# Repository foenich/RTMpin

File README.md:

# RTMpin
This is a pinball project.

A Rollergames playfield was turned into a hybrid pinball machine (pinball firmware via PinMAME like in virtual pinball, but with real playfield and steel balls).

The emulator PinMAME runs on a Raspberry Pi and controls sound, DMD and a few IO-boards underneath the playfield. These in turn read the switch positions and activates the coils and lamps.

To watch a video see documentation folder: rg1stgame.mp4

A word of warning: this is a private, non commercial hobby project. Hardware and software still has errors (see issues and Changes.txt). To make use of anything of this project a basic understanding of electronics and programming is necessary. Nothing of it is "plug and play". I'm surely not liable for any damage to assemblies, pinball machines or even persons.

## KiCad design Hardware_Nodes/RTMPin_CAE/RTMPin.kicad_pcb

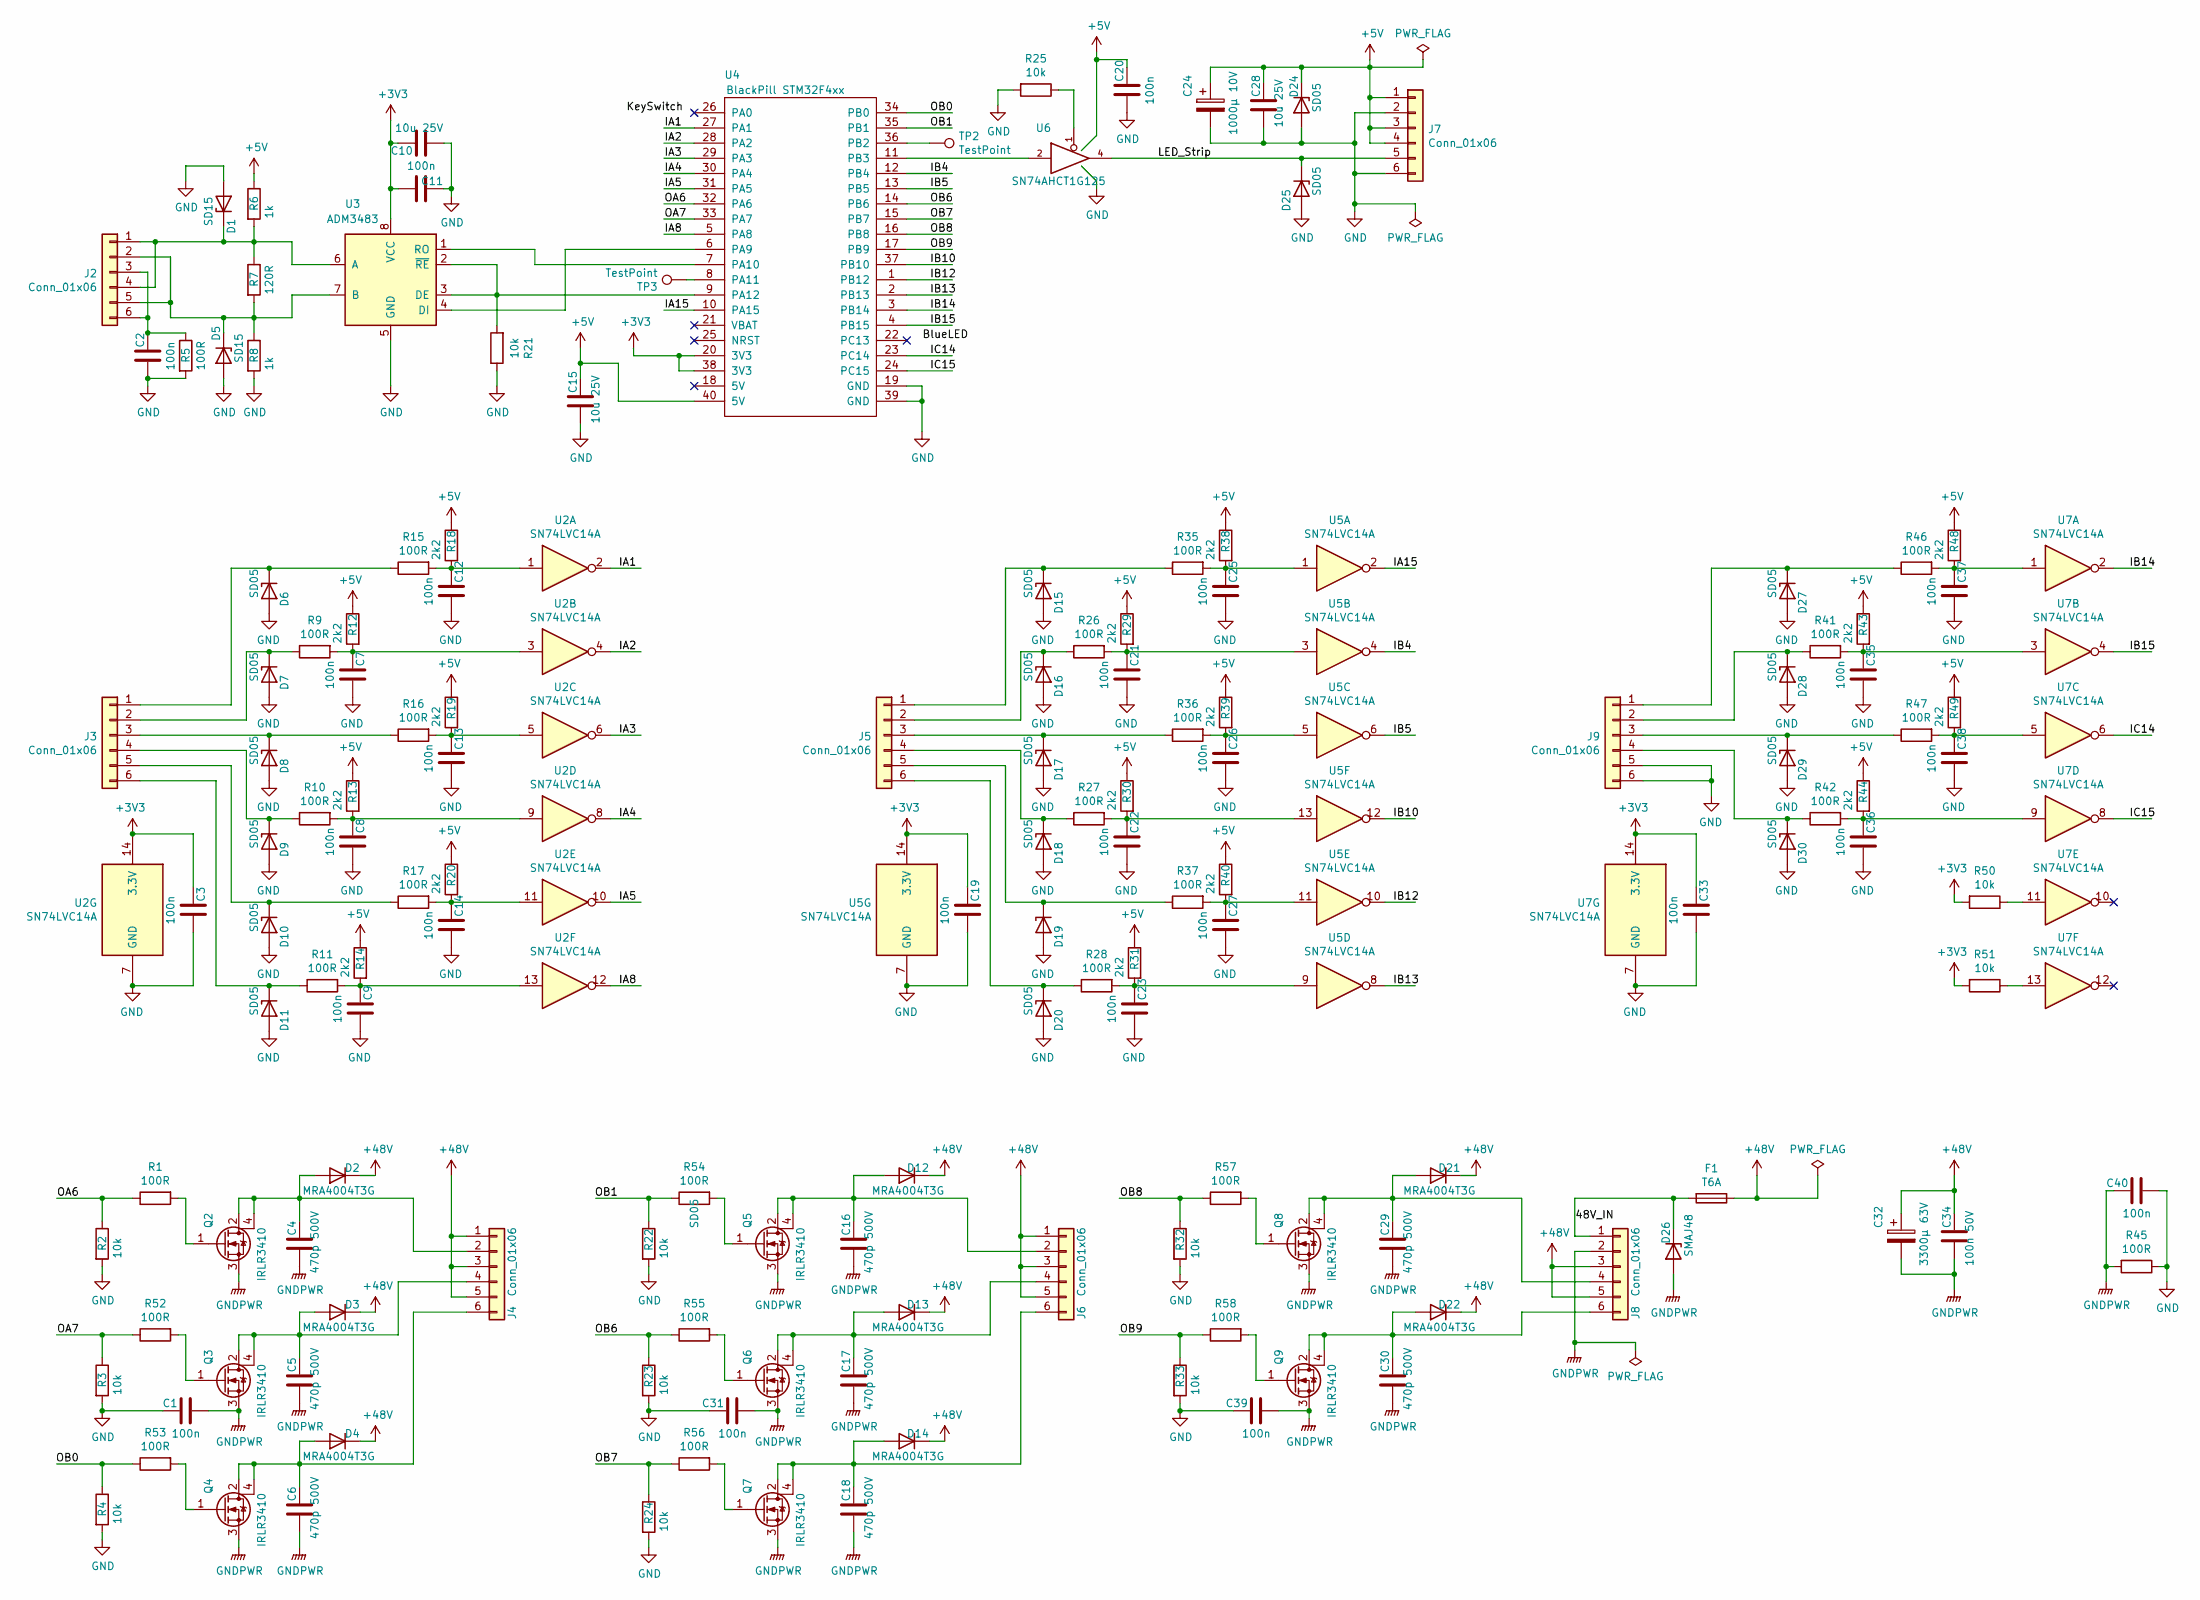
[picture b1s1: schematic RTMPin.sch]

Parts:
C1, C2, C3, C7, C8, C9, C11, C12, C13, C14, C19, C20, C21, C22, C23, C25, C26, C27, C31, C33, C35, C36, C37, C38, C39, C40: 100n; C_0603_1608Metric
C4, C5, C6, C16, C17, C18, C29, C30: 470p 500V; C_1206_3216Metric
C10, C15, C28: 10u 25V; C_1206_3216Metric
C24: 1000µ 10V; CP_Radial_D10.0mm_P5.00mm
C32: 3300µ 63V; CP_Radial_D30.0mm_P10.00mm_SnapIn
C34: 100n 50V; C_0603_1608Metric
D1, D5: SD15; D_SOD-323
D2, D3, D4, D12, D13, D14, D21, D22: MRA4004T3G; D_SMA
D6, D7, D8, D9, D10, D11, D15, D16, D17, D18, D19, D20, D24, D25, D27, D28, D29, D30: SD05; D_SOD-323
D26: SMAJ48; D_SMA
F1: T6A; Fuseholder_Cylinder-5x20mm_Schurter_0031_8201_Horizontal_Op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
J2, J3, J4, J5, J6, J7, J8, J9: Conn_01x06; Terminal_Block_RTMPin
Q2, Q3, Q4, Q5, Q6, Q7, Q8, Q9: IRLR3410; TO-252-3_TabPin4
R1, R5, R9, R10, R11, R15, R16, R17, R26, R27, R28, R35, R36, R37, R41, R42, R45, R46, R47, R52, R53, R54, R55, R56, R57, R58: 100R; R_0603_1608Metric
R2, R3, R4, R21, R22, R23, R24, R25, R32, R33, R50, R51: 10k; R_0603_1608Metric
R6, R8: 1k; R_0603_1608Metric
R7: 120R; R_0603_1608Metric
R12, R13, R14, R18, R19, R20, R29, R30, R31, R38, R39, R40, R43, R44, R48, R49: 2k2; R_0603_1608Metric
TP2, TP3: TestPoint; TestPoint_Pad_D1.5mm
U2, U5, U7: SN74LVC14A; SO-14_3.9x8.65mm_P1.27mm
U3: ADM3483; SOIC-8_3.9x4.9mm_P1.27mm
U4: BlackPill STM32F4xx; DIP-40_W15.24mm_Socket_LongPads
U6: SN74AHCT1G125; SOT-23-5

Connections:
+3V3: C3.1, C10.1, C11.1, C19.1, C33.1, R50.2, R51.2, U2.14 (3.3V), U3.8 (VCC), U4.20 (3V3), U4.38 (3V3), U5.14 (3.3V), U7.14 (3.3V)
+5V: C15.1, C20.1, C24.1, C28.1, D24.1 (K), J7.1, J7.3, J7.4, R6.1, R12.1, R13.1, R14.1, R18.1, R19.1, R20.1, R29.1, R30.1, R31.1, R38.1, R39.1, R40.1, R43.1, R44.1, R48.1, R49.1, U4.40 (5V), U6.5 (VCC)
+48V: C32.1, C34.1, D2.1 (K), D3.1 (K), D4.1 (K), D12.1 (K), D13.1 (K), D14.1 (K), D21.1 (K), D22.1 (K), F1.1, J4.1, J4.3, J4.5, J6.1, J6.3, J6.5, J8.3, J8.5
/48V_IN: D26.1 (K), F1.2, J8.1
/IA1: U2.2, U4.27 (PA1)
/IA2: U2.4, U4.28 (PA2)
/IA3: U2.6, U4.29 (PA3)
/IA4: U2.8, U4.30 (PA4)
/IA5: U2.10, U4.31 (PA5)
/IA8: U2.12, U4.5 (PA8)
/IA15: U4.10 (PA15), U5.2
/IB4: U4.12 (PB4), U5.4
/IB5: U4.13 (PB5), U5.6
/IB10: U4.37 (PB10), U5.12
/IB12: U4.1 (PB12), U5.10
/IB13: U4.2 (PB13), U5.8
/IB14: U4.3 (PB14), U7.2
/IB15: U4.4 (PB15), U7.4
/IC14: U4.23 (PC14), U7.6
/IC15: U4.24 (PC15), U7.8
/LED_Strip: D25.1 (K), J7.5, U6.4
/OA6: R1.1, R2.1, U4.32 (PA6)
/OA7: R3.1, R52.1, U4.33 (PA7)
/OB0: R4.1, R53.1, U4.34 (PB0)
/OB1: R22.1, R54.1, U4.35 (PB1)
/OB6: R23.1, R55.1, U4.14 (PB6)
/OB7: R24.1, R56.1, U4.15 (PB7)
/OB8: R32.1, R57.1, U4.16 (PB8)
/OB9: R33.1, R58.1, U4.17 (PB9)
GND: C1.1, C2.2, C3.2, C7.2, C8.2, C9.2, C10.2, C11.2, C12.2, C13.2, C14.2, C15.2, C19.2, C20.2, C21.2, C22.2, C23.2, C24.2, C25.2, C26.2, C27.2, C28.2, C31.1, C33.2, C35.2, C36.2, C37.2, C38.2, C39.1, C40.2, D1.2 (A), D5.2 (A), D6.2 (A), D7.2 (A), D8.2 (A), D9.2 (A), D10.2 (A), D11.2 (A), D15.2 (A), D16.2 (A), D17.2 (A), D18.2 (A), D19.2 (A), D20.2 (A), D24.2 (A), D25.2 (A), D27.2 (A), D28.2 (A), D29.2 (A), D30.2 (A), J7.2, J7.6, J9.5, J9.6, R2.2, R3.2, R4.2, R5.2, R8.2, R21.1, R22.2, R23.2, R24.2, R25.2, R32.2, R33.2, R45.1, U2.7 (GND), U3.5 (GND), U4.19 (GND), U4.39 (GND), U5.7 (GND), U6.3 (GND), U7.7 (GND)
GNDPWR: C1.2, C4.2, C5.2, C6.2, C16.2, C17.2, C18.2, C29.2, C30.2, C31.2, C32.2, C34.2, C39.2, C40.1, D26.2 (A), J8.2, Q2.3 (S), Q3.3 (S), Q4.3 (S), Q5.3 (S), Q6.3 (S), Q7.3 (S), Q8.3 (S), Q9.3 (S), R45.2
unnamed: C2.1, J2.3, J2.6, R5.1
unnamed: C4.1, D2.2 (A), J4.2, Q2.2 (D), Q2.4 (D)
unnamed: C5.1, D3.2 (A), J4.4, Q3.2 (D), Q3.4 (D)
unnamed: C6.1, D4.2 (A), J4.6, Q4.2 (D), Q4.4 (D)
unnamed: C7.1, R9.2, R12.2, U2.3
unnamed: C8.1, R10.2, R13.2, U2.9
unnamed: C9.1, R11.2, R14.2, U2.13
unnamed: C12.1, R15.2, R18.2, U2.1
unnamed: C13.1, R16.2, R19.2, U2.5
unnamed: C14.1, R17.2, R20.2, U2.11
unnamed: C16.1, D12.2 (A), J6.2, Q5.2 (D), Q5.4 (D)
unnamed: C17.1, D13.2 (A), J6.4, Q6.2 (D), Q6.4 (D)
unnamed: C18.1, D14.2 (A), J6.6, Q7.2 (D), Q7.4 (D)
unnamed: C21.1, R26.2, R29.2, U5.3
unnamed: C22.1, R27.2, R30.2, U5.13
unnamed: C23.1, R28.2, R31.2, U5.9
unnamed: C25.1, R35.2, R38.2, U5.1
unnamed: C26.1, R36.2, R39.2, U5.5
unnamed: C27.1, R37.2, R40.2, U5.11
unnamed: C29.1, D21.2 (A), J8.4, Q8.2 (D), Q8.4 (D)
unnamed: C30.1, D22.2 (A), J8.6, Q9.2 (D), Q9.4 (D)
unnamed: C35.1, R41.2, R43.2, U7.3
unnamed: C36.1, R42.2, R44.2, U7.9
unnamed: C37.1, R46.2, R48.2, U7.1
unnamed: C38.1, R47.2, R49.2, U7.5
unnamed: D1.1 (K), J2.1, J2.4, R6.2, R7.1, U3.6 (A)
unnamed: D5.1 (K), J2.2, J2.5, R7.2, R8.1, U3.7 (B)
unnamed: D6.1 (K), J3.1, R15.1
unnamed: D7.1 (K), J3.2, R9.1
unnamed: D8.1 (K), J3.3, R16.1
unnamed: D9.1 (K), J3.4, R10.1
unnamed: D10.1 (K), J3.5, R17.1
unnamed: D11.1 (K), J3.6, R11.1
unnamed: D15.1 (K), J5.1, R35.1
unnamed: D16.1 (K), J5.2, R26.1
unnamed: D17.1 (K), J5.3, R36.1
unnamed: D18.1 (K), J5.4, R27.1
unnamed: D19.1 (K), J5.5, R37.1
unnamed: D20.1 (K), J5.6, R28.1
unnamed: D27.1 (K), J9.1, R46.1
unnamed: D28.1 (K), J9.2, R41.1
unnamed: D29.1 (K), J9.3, R47.1
unnamed: D30.1 (K), J9.4, R42.1
unnamed: Q2.1 (G), R1.2
unnamed: Q3.1 (G), R52.2
unnamed: Q4.1 (G), R53.2
unnamed: Q5.1 (G), R54.2
unnamed: Q6.1 (G), R55.2
unnamed: Q7.1 (G), R56.2
unnamed: Q8.1 (G), R57.2
unnamed: Q9.1 (G), R58.2
unnamed: R21.2, U3.2 (~RE~), U3.3 (DE), U4.9 (PA12)
unnamed: R25.1, U6.1
unnamed: R50.1, U7.11
unnamed: R51.1, U7.13
unnamed: TP2.1, U4.36 (PB2)
unnamed: TP3.1, U4.8 (PA11)
unnamed: U3.1 (RO), U4.7 (PA10)
unnamed: U3.4 (DI), U4.6 (PA9)
unnamed: U4.11 (PB3), U6.2

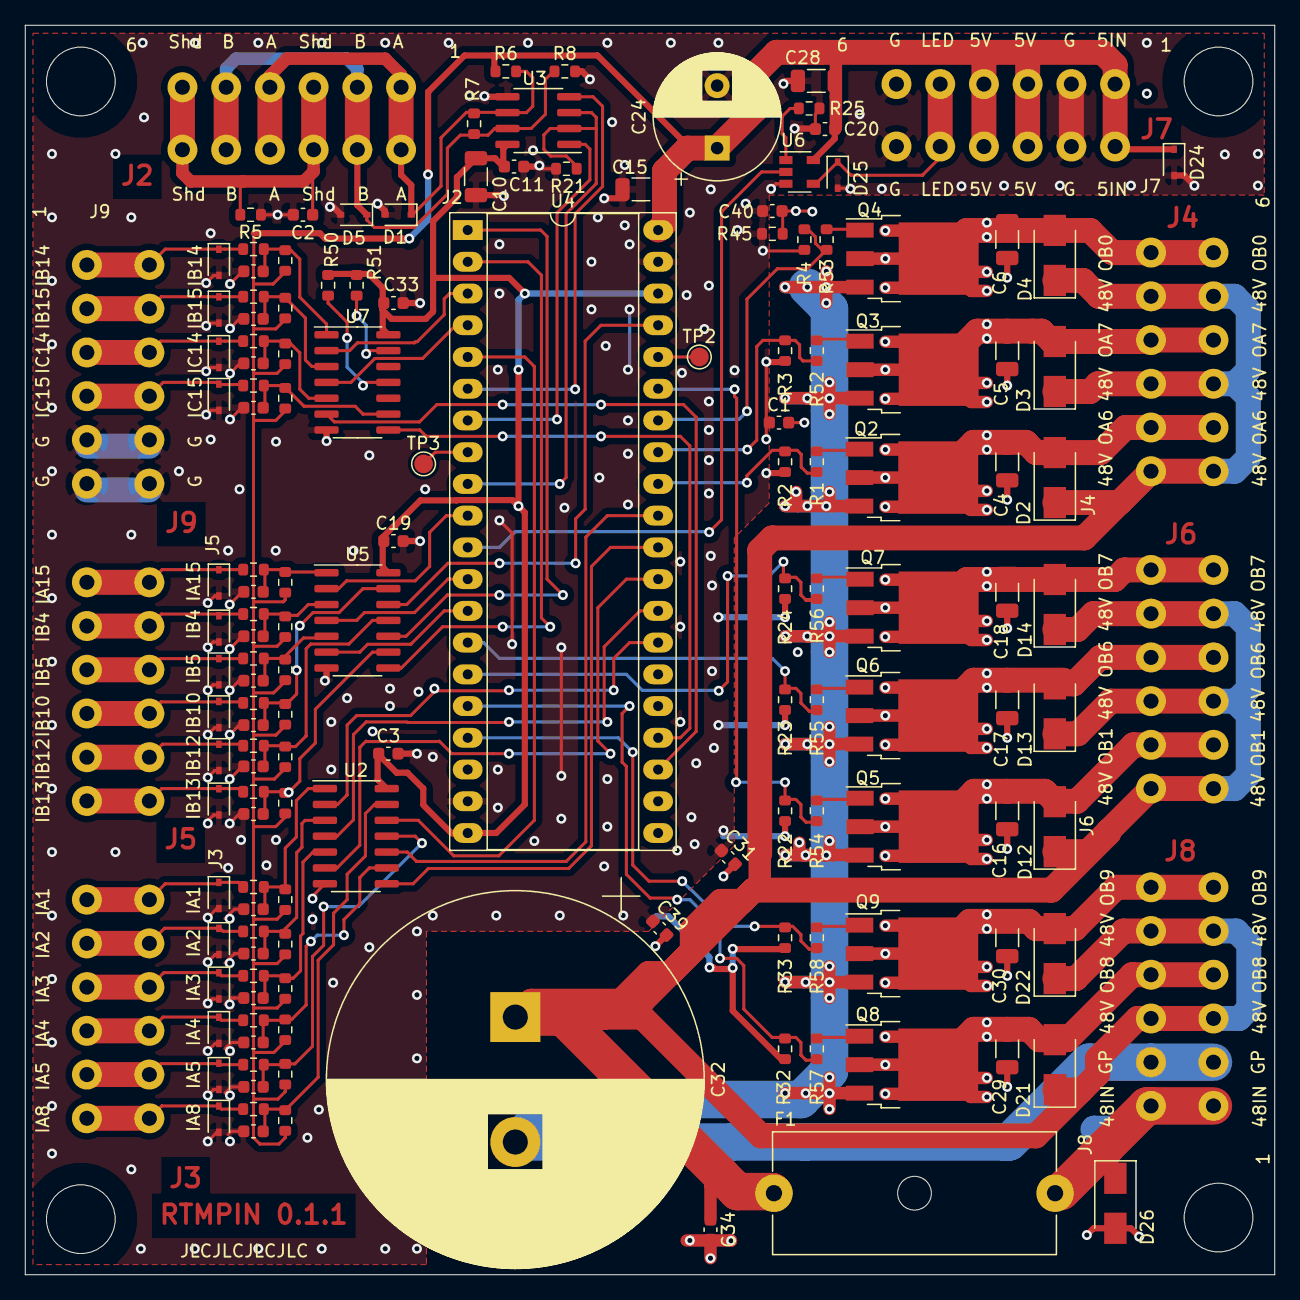
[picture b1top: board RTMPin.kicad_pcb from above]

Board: 2 copper layers, 100.0 x 100.0 mm, 151 parts (0 on the bottom side), 91 nets.

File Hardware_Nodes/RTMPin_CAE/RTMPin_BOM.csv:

Reference, Quantity, Value, Footprint, Datasheet
C10 C15 C28 ,3,"10u 25V","Capacitor_SMD:C_1206_3216Metric","~"
C1 C2 C3 C7 C8 C9 C11 C12 C13 C14 C19 C20 C21 C22 C23 C25 C26 C27 C31 C33 C35 C36 C37 C38 C39 C40 ,26,"100n","Capacitor_SMD:C_0603_1608Metric","~"
C24 ,1,"1000µ 10V","Capacitor_THT:CP_Radial_D10.0mm_P5.00mm","~"
C4 C5 C6 C16 C17 C18 C29 C30 ,8,"470p 500V","Capacitor_SMD:C_1206_3216Metric","~"
C32 ,1,"3300µ 63V","Capacitor_THT:CP_Radial_D30.0mm_P10.00mm_SnapIn","~"
C34 ,1,"100n 50V","Capacitor_SMD:C_0603_1608Metric","~"
D2 D3 D4 D12 D13 D14 D21 D22 ,8,"MRA4004T3G","Diode_SMD:D_SMA","http://www.onsemi.com/pub_link/Collateral/MRA4003T3-D.PDF"
D6 D7 D8 D9 D10 D11 D15 D16 D17 D18 D19 D20 D24 D25 D27 D28 D29 D30 ,18,"SD05","Diode_SMD:D_SOD-323","~"
D26 ,1,"SMAJ48","Diode_SMD:D_SMA","~"
D1 D5 ,2,"SD15","Diode_SMD:D_SOD-323","~"
F1 ,1,"T6A","Fuse:Fuseholder_Cylinder-5x20mm_Schurter_0031_8201_Horizontal_Open","~"
J2 J3 J4 J5 J6 J7 J8 J9 ,8,"Conn_01x06","RTMPin_CAE:Terminal_Block_RTMPin","~"
Q2 Q3 Q4 Q5 Q6 Q7 Q8 Q9 ,8,"IRLR3410","Package_TO_SOT_SMD:TO-252-3_TabPin4","~"
R2 R3 R4 R21 R22 R23 R24 R25 R32 R33 R50 R51 ,12,"10k","Resistor_SMD:R_0603_1608Metric","~"
R12 R13 R14 R18 R19 R20 R29 R30 R31 R38 R39 R40 R43 R44 R48 R49 ,16,"2k2","Resistor_SMD:R_0603_1608Metric","~"
R1 R5 R9 R10 R11 R15 R16 R17 R26 R27 R28 R35 R36 R37 R41 R42 R45 R46 R47 R52 R53 R54 R55 R56 R57 R58 ,26,"100R","Resistor_SMD:R_0603_1608Metric","~"
R6 R8 ,2,"1k","Resistor_SMD:R_0603_1608Metric","~"
R7 ,1,"120R","Resistor_SMD:R_0603_1608Metric","~"
TP2 TP3 ,2,"TestPoint","TestPoint:TestPoint_Pad_D1.5mm","~"
U3 ,1,"ADM3483","Package_SO:SOIC-8_3.9x4.9mm_P1.27mm","http://www.icbase.com/pdf/SPX/SPX00480106.pdf"
U4 ,1,"BlackPill STM32F4xx","Package_DIP:DIP-40_W15.24mm_Socket_LongPads",""
U2 U5 U7 ,3,"SN74LVC14A","Package_SO:SO-14_3.9x8.65mm_P1.27mm","http://www.ti.com/lit/gpn/sn74LV14"
U6 ,1,"SN74AHCT1G125","Package_TO_SOT_SMD:SOT-23-5",""

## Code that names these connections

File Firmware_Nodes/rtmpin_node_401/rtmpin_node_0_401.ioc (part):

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Mcu.Name=STM32F401C(B-C)Ux
Mcu.Package=UFQFPN48
Mcu.UserName=STM32F401CCUx
PA0-WKUP.GPIOParameters=GPIO_Label
PA0-WKUP.GPIO_Label=KeySwitch
PA0-WKUP.Signal=GPIO_Input
PA1.GPIOParameters=GPIO_PuPd
PA1.GPIO_PuPd=GPIO_PULLUP
PA1.Signal=GPIO_Input
PA10.Mode=Asynchronous
PA10.Signal=USART1_RX
PA11.Signal=S_TIM1_CH4
PA12.GPIOParameters=GPIO_PuPd,GPIO_Label
PA12.GPIO_Label=RS485_nWrite
PA12.GPIO_PuPd=GPIO_NOPULL
PA12.Signal=GPIO_Output
PA13.Mode=Serial_Wire
PA13.Signal=SYS_JTMS-SWDIO
PA14.Mode=Serial_Wire
PA14.Signal=SYS_JTCK-SWCLK
PA15.GPIOParameters=GPIO_PuPd
PA15.GPIO_PuPd=GPIO_PULLUP
PA15.Signal=GPIO_Input
PA2.GPIOParameters=GPIO_PuPd
PA2.GPIO_PuPd=GPIO_PULLUP
PA2.Signal=GPIO_Input
PA3.GPIOParameters=GPIO_PuPd
PA3.GPIO_PuPd=GPIO_PULLUP
PA3.Signal=GPIO_Input
PA4.GPIOParameters=GPIO_PuPd
PA4.GPIO_PuPd=GPIO_PULLUP
PA4.Signal=GPIO_Input
PA5.GPIOParameters=GPIO_PuPd
PA5.GPIO_PuPd=GPIO_PULLUP
PA5.Signal=GPIO_Input
PA6.Signal=S_TIM3_CH1
PA7.Signal=S_TIM3_CH2
PA8.GPIOParameters=GPIO_PuPd
PA8.GPIO_PuPd=GPIO_PULLUP
PA8.Signal=GPIO_Input
PA9.Mode=Asynchronous
PA9.Signal=USART1_TX
PB0.Signal=S_TIM3_CH3
PB1.Signal=S_TIM3_CH4
PB10.GPIOParameters=GPIO_PuPd
PB10.GPIO_PuPd=GPIO_PULLUP
PB10.Signal=GPIO_Input
PB12.GPIOParameters=GPIO_PuPd
PB12.GPIO_PuPd=GPIO_PULLUP
PB12.Signal=GPIO_Input
PB13.GPIOParameters=GPIO_PuPd
PB13.GPIO_PuPd=GPIO_PULLUP
PB13.Signal=GPIO_Input
PB14.GPIOParameters=GPIO_PuPd
PB14.GPIO_PuPd=GPIO_PULLUP
PB14.Signal=GPIO_Input
PB15.GPIOParameters=GPIO_PuPd
PB15.GPIO_PuPd=GPIO_PULLUP
PB15.Signal=GPIO_Input
PB3.Signal=S_TIM2_CH2
PB4.GPIOParameters=GPIO_PuPd
PB4.GPIO_PuPd=GPIO_PULLUP
PB4.Signal=GPIO_Input
PB5.GPIOParameters=GPIO_PuPd
PB5.GPIO_PuPd=GPIO_PULLUP
PB5.Signal=GPIO_Input
PB6.Signal=S_TIM4_CH1
PB7.Signal=S_TIM4_CH2
PB8.Signal=S_TIM4_CH3
PB9.Signal=S_TIM4_CH4
PC13-ANTI_TAMP.GPIOParameters=GPIO_Label
PC13-ANTI_TAMP.GPIO_Label=BlueLED
PC13-ANTI_TAMP.Signal=GPIO_Output
PC14-OSC32_IN.GPIOParameters=GPIO_PuPd
PC14-OSC32_IN.GPIO_PuPd=GPIO_PULLUP
PC14-OSC32_IN.Signal=GPIO_Input
PC15-OSC32_OUT.GPIOParameters=GPIO_PuPd
PC15-OSC32_OUT.GPIO_PuPd=GPIO_PULLUP
PC15-OSC32_OUT.Signal=GPIO_Input
PH0\ -\ OSC_IN.Mode=HSE-External-Oscillator
PH0\ -\ OSC_IN.Signal=RCC_OSC_IN
PH1\ -\ OSC_OUT.Mode=HSE-External-Oscillator
PH1\ -\ OSC_OUT.Signal=RCC_OSC_OUT
RCC.HSE_VALUE=25000000
RCC.SYSCLKFreq_VALUE=84000000
RCC.SYSCLKSource=RCC_SYSCLKSOURCE_PLLCLK
board=custom

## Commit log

2022-08-27 Rename Software_Nodes/README.md to Firmware_Nodes/README.md
2022-08-27 Rename LICENSE to Software_PinMAME/LICENSE
2022-08-27 added license files and folders
2022-08-27 added Firmware_Nodes
2022-08-27 updated README for Firmware_Nodes
2022-08-27 added Hardware_Nodes
2022-08-27 added unix.mak
2022-08-30 more docu
2022-09-01 added schematic_RTMpin.pdf
2022-09-04 updated Changes.txt
2022-09-30 added RTMPin-cache.lib
2022-09-30 changed gitinore to subdirs
2022-09-30 HW bugfix
2022-09-30 Schematic pdf updated
2022-10-01 all parts on top side
2022-10-02 added xsl
2022-10-02 rm Gerber
2022-10-02 rm xsl added BOM
2022-10-03 tvs unipolar
2022-10-29 added JD
2022-10-29 updated .gitignore
2022-10-29 updated gitignore
2022-11-14 fixed update and debounce flipper
2022-11-14 fix update in JDonRG
2022-11-19 JD special functions
